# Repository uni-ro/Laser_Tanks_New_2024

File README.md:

# Laser Tanks
Laser Tanks is a project run by the Curtin Robotics Club.
Our aim is to make a game of laser tag that is played with remote controlled tanks.
hi from james

## Contents
- [Code](https://github.com/curtinrobotics/Laser_Tanks_New_2024/tree/master/Code)
- [Laser Reciever](https://github.com/curtinrobotics/Laser_Tanks_New_2024/tree/master/Laser%20Receiver)
- [Tank CAD Model](https://github.com/curtinrobotics/Laser_Tanks_New_2024/tree/master/Tank%20CAD%20Model)
- [Tank Motherboard](https://github.com/curtinrobotics/Laser_Tanks_New_2024/tree/master/Tank%20Motherboard)

***

### CAD model
This is the documentation for the tank CAD model.
![[CAD Model#Summary]]

***

### Motherboard
This is the documentation for the tank motherboard.

![[Tank Motherboard]]

***

### Microcontroller Programming  
![[How to write and upload code]]

***

### Remote microcontroller programming  

***

### Laser Detection  

***

### Map Design  

***

### RFID

***

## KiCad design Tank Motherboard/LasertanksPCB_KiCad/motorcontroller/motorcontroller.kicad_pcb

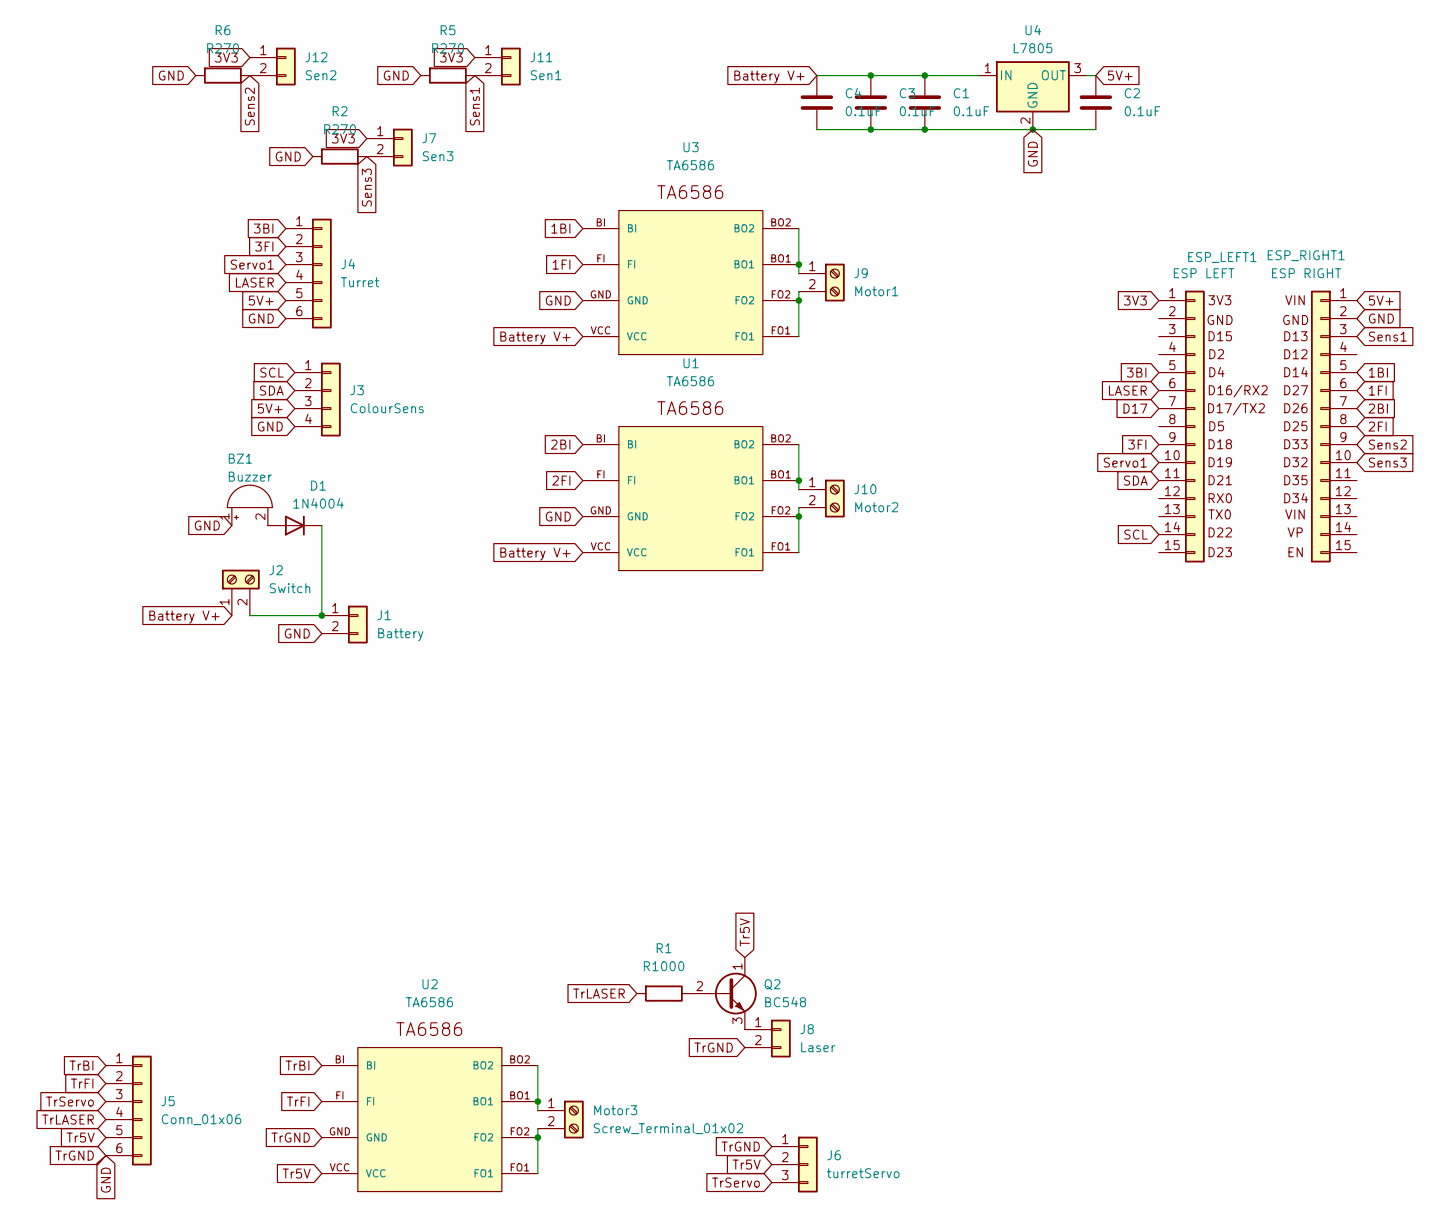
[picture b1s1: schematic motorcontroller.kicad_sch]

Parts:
BZ1: Buzzer; Buzzer_12x9.5RM7.6
C1, C2, C3, C4: 0.1uF; C_Rect_L9.0mm_W2.5mm_P7.50mm_MKT
D1: 1N4004; D_DO-41_SOD81_P10.16mm_Horizontal
ESP_LEFT1: ESP LEFT; PinHeader_1x15_P2.54mm_Vertical
ESP_RIGHT1: ESP RIGHT; PinHeader_1x15_P2.54mm_Vertical
J1: Battery; PinHeader_1x02_P2.54mm_Horizontal
J2: Switch; TerminalBlock_4Ucon_1x02_P3.50mm_Horizontal
J3: ColourSens; JST_XH_S4B-XH-A_1x04_P2.50mm_Horizontal
J4: Turret; JST_XH_S6B-XH-A_1x06_P2.50mm_Horizontal
J5: Conn_01x06; JST_XH_S6B-XH-A-1_1x06_P2.50mm_Horizontal
J6: turretServo; PinHeader_1x03_P2.54mm_Vertical
J7: Sen3; JST_XH_S2B-XH-A_1x02_P2.50mm_Horizontal
J8: Laser; PinHeader_1x02_P2.54mm_Vertical
J9: Motor1; TerminalBlock_4Ucon_1x02_P3.50mm_Horizontal
J10: Motor2; TerminalBlock_4Ucon_1x02_P3.50mm_Horizontal
J11: Sen1; JST_XH_S2B-XH-A_1x02_P2.50mm_Horizontal
J12: Sen2; JST_XH_S2B-XH-A_1x02_P2.50mm_Horizontal
Motor3: Screw_Terminal_01x02; TerminalBlock_4Ucon_1x02_P3.50mm_Horizontal
Q2: BC548; TO-92_Inline
R1: R1000; R_Axial_DIN0207_L6.3mm_D2.5mm_P7.62mm_Horizontal
R2, R5, R6: R270; R_Axial_DIN0207_L6.3mm_D2.5mm_P10.16mm_Horizontal
U1, U2, U3: TA6586; TA6586-FOOTPRINT
U4: L7805; TO-220F-3_Vertical

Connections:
1BI: ESP_RIGHT1.5 (D14), U3.BI
1FI: ESP_RIGHT1.6 (D27), U3.FI
2BI: ESP_RIGHT1.7 (D26), U1.BI
2FI: ESP_RIGHT1.8 (D25), U1.FI
3BI: ESP_LEFT1.5 (D4), J4.1
3FI: ESP_LEFT1.9 (D18), J4.2
3V3: ESP_LEFT1.1 (3V3), J7.1, J11.1, J12.1
5V+: C2.1, ESP_RIGHT1.1 (VIN), J3.3, J4.5, U4.3 (OUT)
Battery V+: C1.1, C3.1, C4.1, J2.1, U1.VCC, U3.VCC, U4.1 (IN)
D17: ESP_LEFT1.7 (D17)
GND: BZ1.1 (+), C1.2, C2.2, C3.2, C4.2, ESP_RIGHT1.2 (GND), J1.2, J3.4, J4.6, J5.6, J6.1, J8.2, R2.2, R5.2, R6.2, U1.GND, U2.GND, U3.GND, U4.2 (GND)
LASER: ESP_LEFT1.6 (D16), J4.4
unnamed: BZ1.2 (-), D1.2 (A)
unnamed: D1.1 (K), J1.1, J2.2
unnamed: J8.1, Q2.3 (E)
unnamed: J9.1, U3.BO1, U3.BO2
unnamed: J9.2, U3.FO1, U3.FO2
unnamed: J10.1, U1.BO1, U1.BO2
unnamed: J10.2, U1.FO1, U1.FO2
unnamed: Motor3.1, U2.BO1, U2.BO2
unnamed: Motor3.2, U2.FO1, U2.FO2
unnamed: Q2.2 (B), R1.1
SCL: ESP_LEFT1.14 (D22), J3.1
SDA: ESP_LEFT1.11 (D21), J3.2
Sens1: ESP_RIGHT1.3 (D13), J11.2, R5.1
Sens2: ESP_RIGHT1.9 (D33), J12.2, R6.1
Sens3: ESP_RIGHT1.10 (D32), J7.2, R2.1
Servo1: ESP_LEFT1.10 (D19), J4.3
Tr5V: J5.5, J6.2, Q2.1 (C), U2.VCC
TrBI: J5.1, U2.BI
TrFI: J5.2, U2.FI
TrLASER: J5.4, R1.2
TrServo: J5.3, J6.3

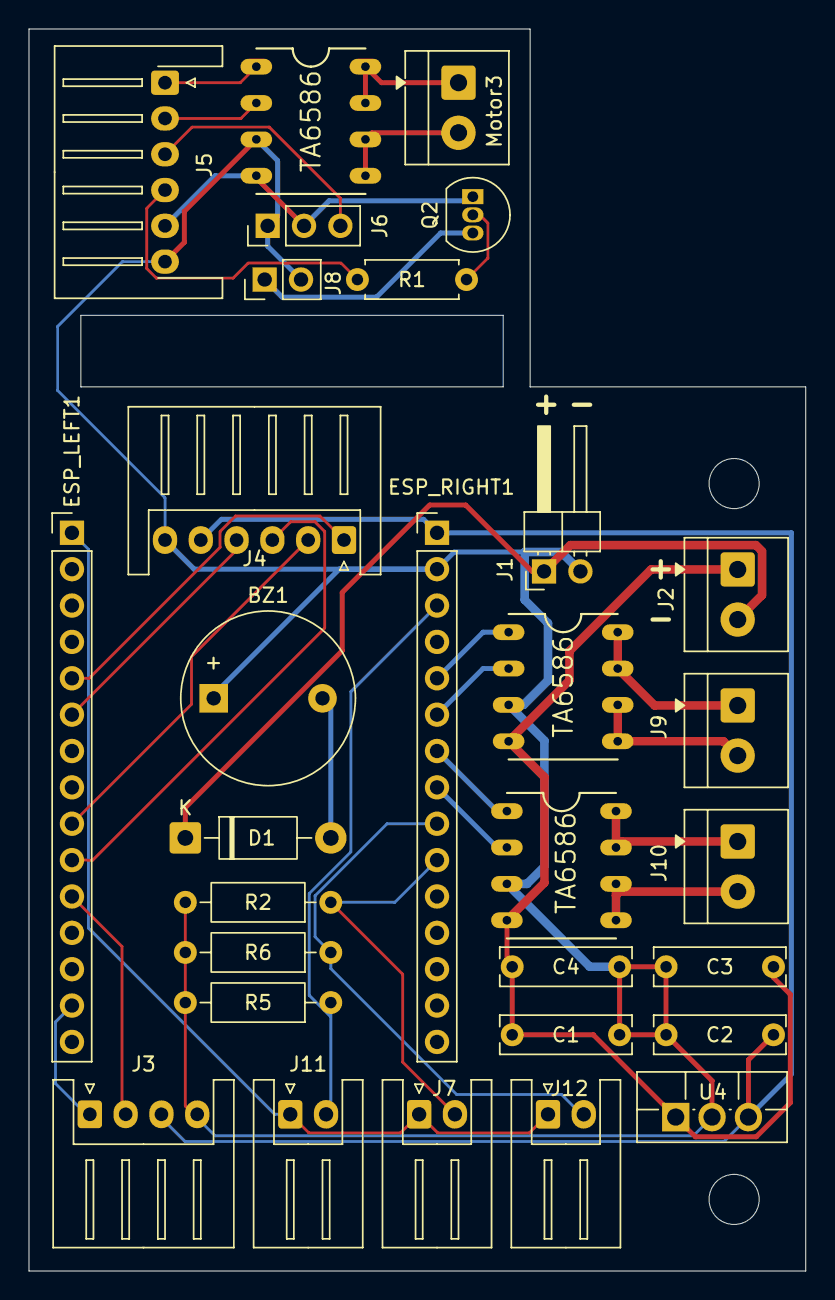
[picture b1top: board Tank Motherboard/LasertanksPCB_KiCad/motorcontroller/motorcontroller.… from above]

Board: 2 copper layers, 54.2 x 86.8 mm, 30 parts (0 on the bottom side), 32 nets.

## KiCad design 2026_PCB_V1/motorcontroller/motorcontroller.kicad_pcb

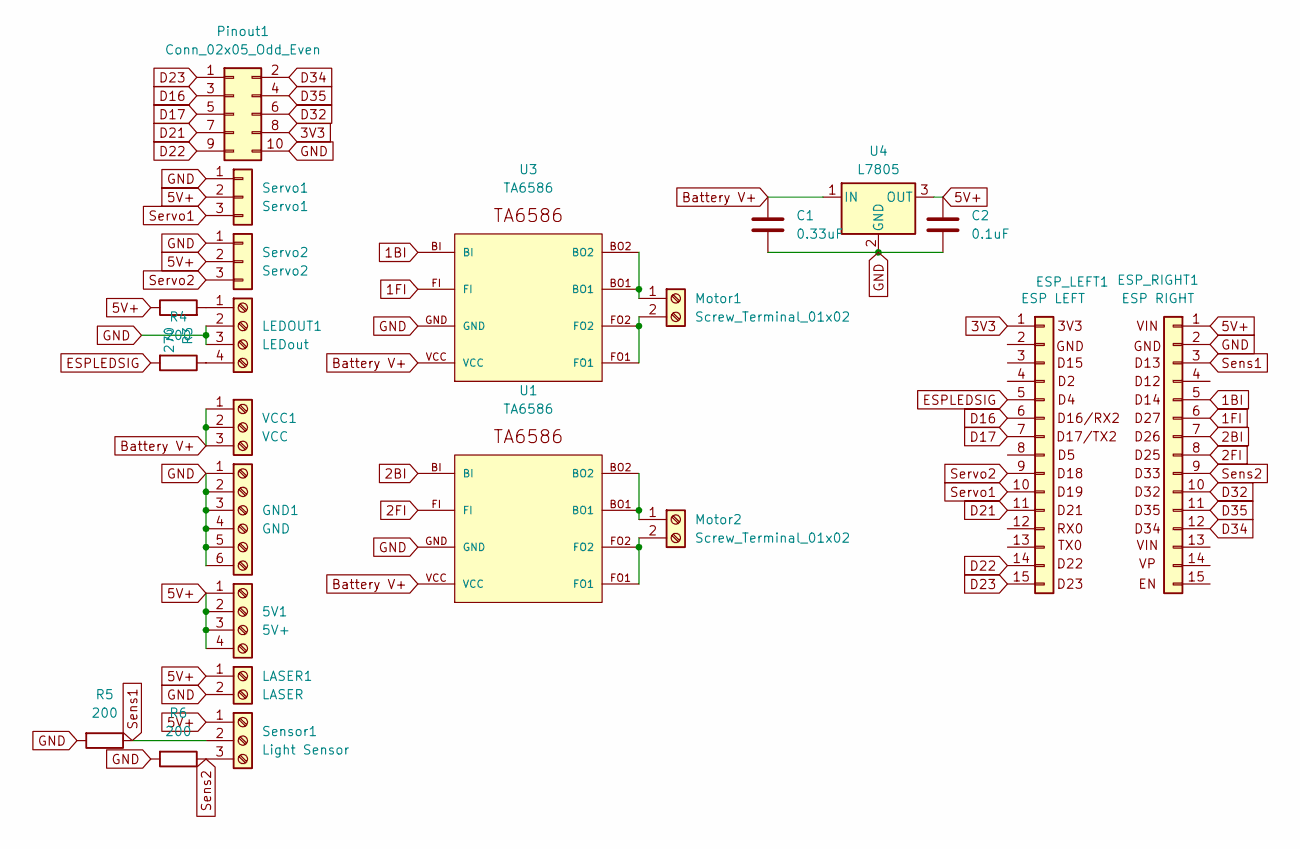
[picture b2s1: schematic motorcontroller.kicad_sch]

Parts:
5V1: 5V+; TerminalBlock_4Ucon_1x04_P3.50mm_Horizontal
C1: 0.33uF; C_Rect_L9.0mm_W2.5mm_P7.50mm_MKT
C2: 0.1uF; C_Rect_L9.0mm_W2.5mm_P7.50mm_MKT
ESP_LEFT1: ESP LEFT; PinHeader_1x15_P2.54mm_Vertical
ESP_RIGHT1: ESP RIGHT; PinHeader_1x15_P2.54mm_Vertical
GND1: GND; TerminalBlock_4Ucon_1x06_P3.50mm_Horizontal
LASER1: LASER; TerminalBlock_4Ucon_1x02_P3.50mm_Horizontal
LEDOUT1: LEDout; TerminalBlock_4Ucon_1x04_P3.50mm_Horizontal
Motor1, Motor2: Screw_Terminal_01x02; TerminalBlock_4Ucon_1x02_P3.50mm_Horizontal
Pinout1: Conn_02x05_Odd_Even; PinHeader_2x05_P2.54mm_Vertical
R3: 270; R_Axial_DIN0207_L6.3mm_D2.5mm_P10.16mm_Horizontal
R4, R5, R6: 200; R_Axial_DIN0207_L6.3mm_D2.5mm_P10.16mm_Horizontal
Sensor1: Light Sensor; TerminalBlock_4Ucon_1x03_P3.50mm_Horizontal
Servo1: Servo1; PinHeader_1x03_P2.54mm_Vertical
Servo2: Servo2; PinHeader_1x03_P2.54mm_Vertical
U1, U3: TA6586; TA6586-FOOTPRINT
U4: L7805; TO-220F-3_Vertical
VCC1: VCC; TerminalBlock_4Ucon_1x03_P3.50mm_Horizontal

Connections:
1BI: ESP_RIGHT1.5 (D14), U3.BI
1FI: ESP_RIGHT1.6 (D27), U3.FI
2BI: ESP_RIGHT1.7 (D26), U1.BI
2FI: ESP_RIGHT1.8 (D25), U1.FI
3V3: ESP_LEFT1.1 (3V3), Pinout1.8
5V+: 5V1.1, 5V1.2, 5V1.3, 5V1.4, C2.1, ESP_RIGHT1.1 (VIN), LASER1.1, R3.1, Sensor1.1, Servo1.2, Servo2.2, U4.3 (OUT)
Battery V+: C1.1, U1.VCC, U3.VCC, U4.1 (IN), VCC1.1, VCC1.2, VCC1.3
D16: ESP_LEFT1.6 (D16), Pinout1.3
D17: ESP_LEFT1.7 (D17), Pinout1.5
D21: ESP_LEFT1.11 (D21), Pinout1.7
D22: ESP_LEFT1.14 (D22), Pinout1.9
D23: ESP_LEFT1.15 (D23), Pinout1.1
D32: ESP_RIGHT1.10 (D32), Pinout1.6
D34: ESP_RIGHT1.12 (D34), Pinout1.2
D35: ESP_RIGHT1.11 (D35), Pinout1.4
ESPLEDSIG: ESP_LEFT1.5 (D4), R4.2
GND: C1.2, C2.2, ESP_RIGHT1.2 (GND), GND1.1, GND1.2, GND1.3, GND1.4, GND1.5, GND1.6, LASER1.2, LEDOUT1.2, LEDOUT1.3, Pinout1.10, R5.2, R6.2, Servo1.1, Servo2.1, U1.GND, U3.GND, U4.2 (GND)
unnamed: LEDOUT1.1, R3.2
unnamed: LEDOUT1.4, R4.1
unnamed: Motor1.1, U3.BO1, U3.BO2
unnamed: Motor1.2, U3.FO1, U3.FO2
unnamed: Motor2.1, U1.BO1, U1.BO2
unnamed: Motor2.2, U1.FO1, U1.FO2
Sens1: ESP_RIGHT1.3 (D13), R5.1, Sensor1.2
Sens2: ESP_RIGHT1.9 (D33), R6.1, Sensor1.3
Servo1: ESP_LEFT1.10 (D19), Servo1.3
Servo2: ESP_LEFT1.9 (D18), Servo2.3

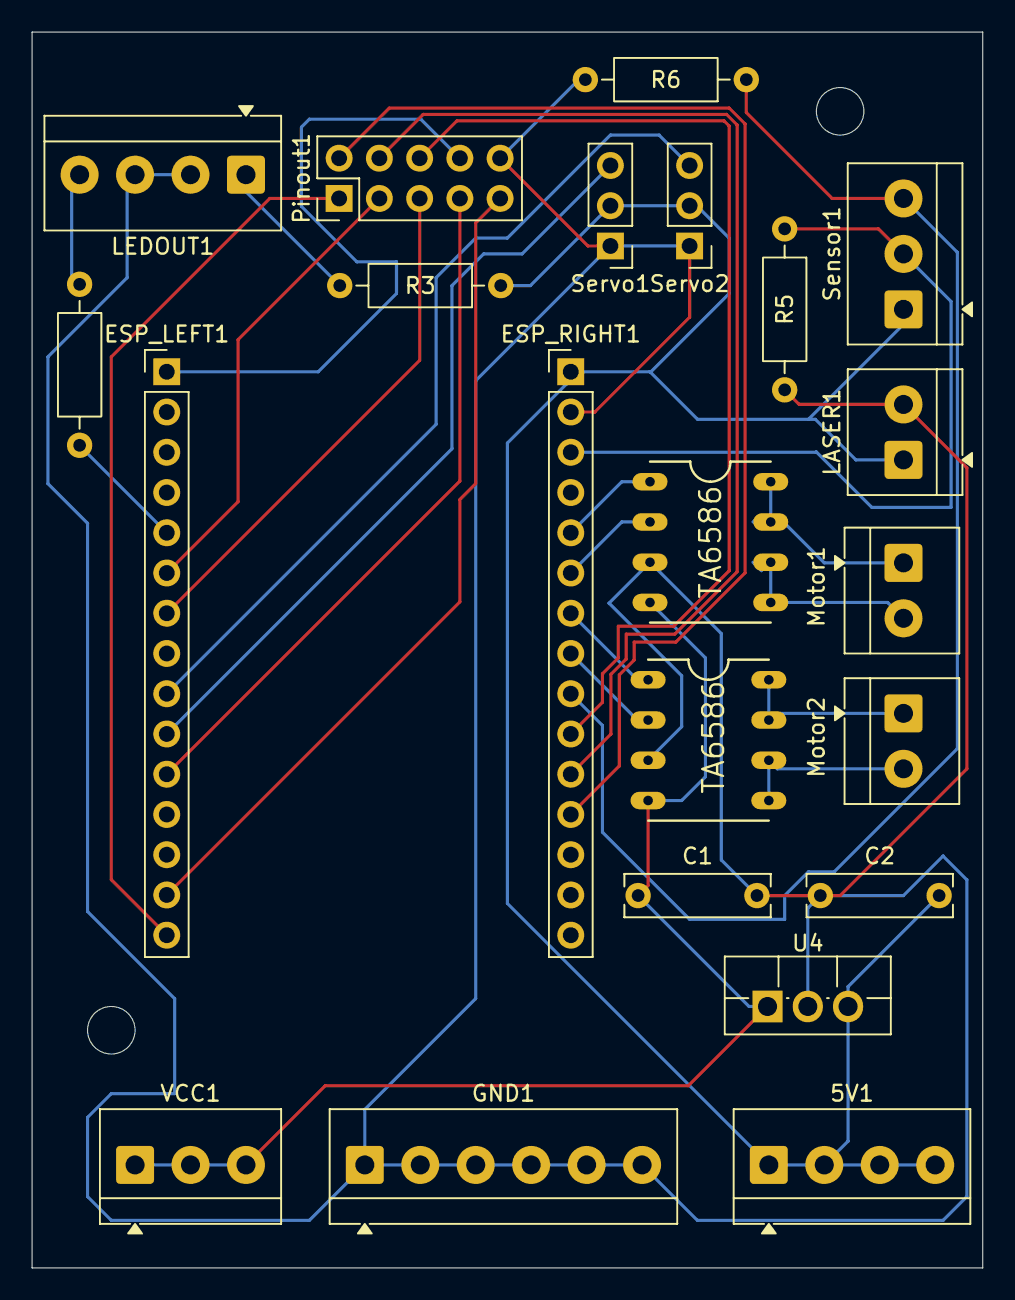
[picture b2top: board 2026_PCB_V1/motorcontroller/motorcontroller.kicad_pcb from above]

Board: 2 copper layers, 60.0 x 78.0 mm, 22 parts (0 on the bottom side), 27 nets.

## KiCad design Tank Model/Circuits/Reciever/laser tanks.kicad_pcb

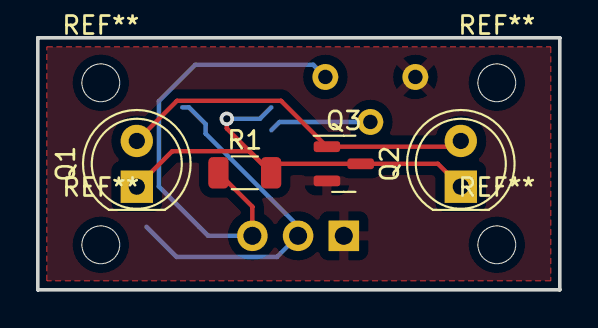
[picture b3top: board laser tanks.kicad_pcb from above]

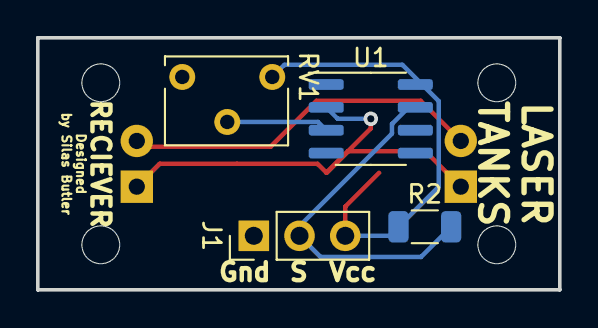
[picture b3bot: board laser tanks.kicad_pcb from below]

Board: 2 copper layers, 29.0 x 14.0 mm, 8 parts (4 on the bottom side), 6 nets.

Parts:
J1: Conn_01x03_Male; PinHeader_1x03_P2.54mm_Vertical
Q1, Q2: Q_Photo_NPN; LED_D5.0mm
Q3: BC846; SOT-23
R1, R2: 1k; R_1206_3216Metric
RV1: R_Potentiometer_Trim_US; Potentiometer_Vishay_T73XX_Horizontal
U1: LM311; SOIC-8_3.9x4.9mm_P1.27mm

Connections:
GND: J1.1, Q3.2 (E), RV1.3, U1.1 (GND), U1.4 (V-)
unnamed: J1.2, R2.2, U1.7
unnamed: Q1.1 (C), Q2.1 (C), Q3.3 (C), R1.2, U1.2 (+)
unnamed: Q1.2 (E), Q2.2 (E), Q3.1 (B)
unnamed: RV1.2, U1.3 (-)
VCC: J1.3, R1.1, R2.1, RV1.1, U1.8 (V+)

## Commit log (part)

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2024-03-16 Initial commit
    Added tank project project environment.
    This is just an interrupt test which doesnt work :(
    When programming the controller and server, probably going to use the same repository and just have it in different source files.
2024-03-22 Started main program structure
    Started main structure
    Added reading from serial, debugging over serial, and switch wrappers around serial
    Started Laser system, added in shoot functionality
    Started Comms system, added in 'F' to fire the laser
    Cleaned up structure
2024-04-11 Added Drive.c
2024-04-12 Cleanup PWM and Interrupt
    Took the PWM logic out of Drive.c and moved it to PWM.c for more abstraction
    Added the shopping list
2024-05-02 Added Link to word online
2024-08-01 Update Links.txt
    CAD
2024-08-01 Updated motor speeds and mapping
2024-08-10 Added Tank V1 model
2024-08-15 Create 3D Printing files
2024-08-15 ESPNOWtest
2024-08-15 Organising 3d files
2024-08-15 Uploaded receiver circuits
2024-08-15 Added logic for sending serial data to esp now
2024-08-15 Sending string test
2024-08-15 ESP now WORKING!!!!!
2024-08-17 Update Tasks.txt
    Added a better structure for Tasks.txt
2024-08-17 Re organised GIT structure
2024-08-17 Formatted Tasks.md
2024-08-17 fix links in Tasks.md
2024-08-17 Fix formatting in Tasks.md
2024-08-17 Moved Tasks.md into README.md
2024-08-17 Fixed links in README.md
2024-08-22 Update message structure
2024-08-22 TOM code for controller
2024-08-23 Updated : struct
2024-08-23 Updated: Frame
2024-08-23 Network Frame Updated
2024-08-25 Code
2024-08-29 Update README.md
    added me to remote controller
2024-08-29 Updated platoformio.ini in networking
2024-08-29 Test ESP now on ESP32
2024-08-29 Moved Networking into new tank source folder
2024-08-29 Cleaned up directory
2024-08-29 Added Remote Controller - TOM
2024-08-29 Rangeaaaaa
2024-09-12 Select
    Not working
2024-09-19 Two Joysticks :)
2024-09-21 Added Tank Model V2
2024-09-26 upload tank code
2024-09-26 Added motor driver circuit documentation
2024-09-26 Update Lib
2024-09-26 Added Coms to joystick
2024-09-27 Remove unnecessary files
2024-09-27 Create .gitignore
    It is about time we had a propper .gitignore
2024-09-30 Re organised ControllerPC
2024-10-03 Thing
2024-10-03 Update esp now
2024-10-03 Added tank_control.h
2024-10-04 Added battery readout to ControllerPC
2024-10-06 Updated esp_now_util, moved into lib
2025-01-21 Fixed controller code
    The controller now works as expected. The only issue was assigning the analog pins as input pins. That mucks with something, im not sure what
2025-01-23 2 New CAD Versions!!
    Wake up babe, new Laser Tanks commit dropped.
    Added Obsidian documentation
    Added V3 and V4 models
2025-02-10 Added Tank Model V4
2025-02-10 Added Tank Motherboard V2
    Redesigned the motherboard of the last tank to include a spot for the ESP8266 to go. Also improved all aspects of the circuit!
2025-02-13 Improved Tank Motherboard V2
    Added reverse voltage protection in case you connect the LiPo backwards.
    Added a switch to connect / disconnect LiPo +
2025-02-18 Updated tank code and controller code
2025-02-18 Added O-Day instructions
2025-03-06 Working controller code
    Working code for sending data from the controller to the tank
2025-03-06 Controller
    Fixed Controller again
2025-03-06 platform io project configurations
2025-03-12 Commit from 2025S1 Week 2 build night
2025-03-13 Started Tank Motherboard V3
2025-03-13 Create commands.h
    helper functions and macros
2025-03-13 Created a guide for programming and uploading code
2025-03-13 Re organising but have to commit before laptop dies
    Im still half way through re organising
2025-03-19 Almost finished Tank Motherboard V3
    Almost finished routing the new PCB
    Just gotta add the finishing touches
2025-03-20 Added simpler tank controller code
2025-03-21 Added changes from build night on 20th March
2025-03-28 Added finished Tank Motherboard V3 model
2025-04-26 26th April 2025
2025-05-15 Added troubleshooting info for wsl
2025-07-24 Added exported PDF of Tank Motherboard V2
2025-08-07 Added MotherboardV3 pdf schematic
2025-08-14 Moved some images
2025-08-14 Added Altered PCB V4
2025-08-14 Added MotherBoard V4 Gerber
2026-05-14 Added Dual-Core code for detecting laser PWM on isolated core
2026-06-21 Renamed How to write and upload code.md to README.md
    Renamed the aforementioned markdown to readme to allow for easy merging between upstream and current fork.
